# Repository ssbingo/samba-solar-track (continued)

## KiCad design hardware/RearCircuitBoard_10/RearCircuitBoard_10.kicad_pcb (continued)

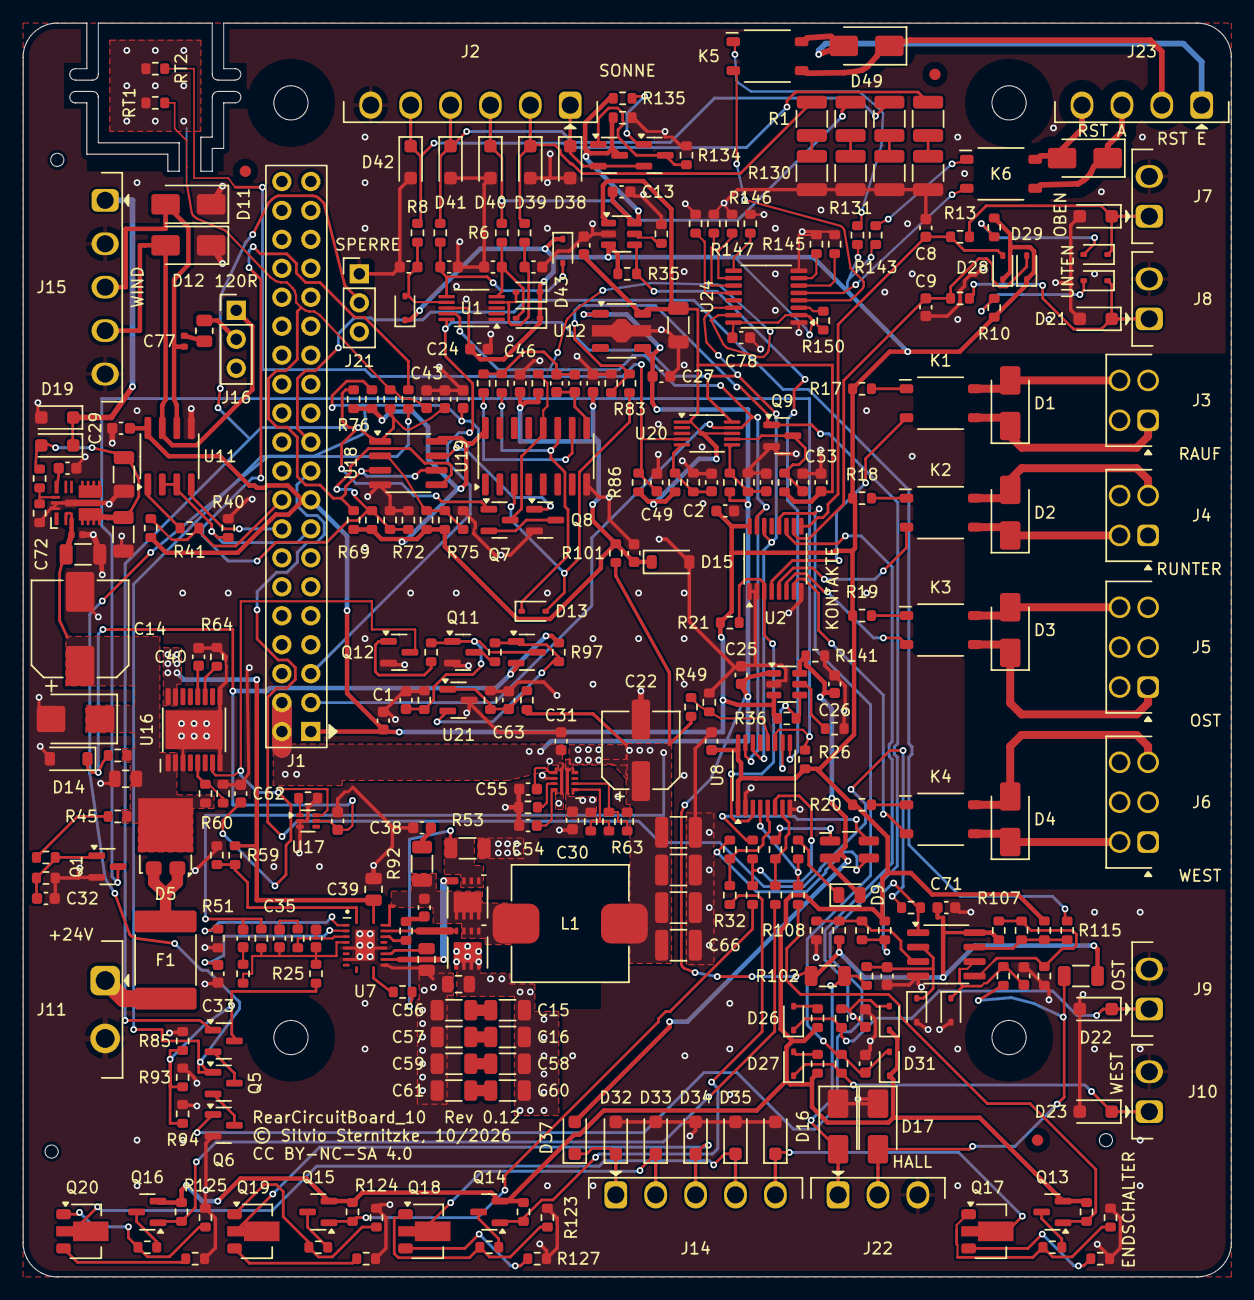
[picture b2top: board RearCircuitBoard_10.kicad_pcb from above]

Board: 4 copper layers, 106.0 x 110.0 mm, 345 parts (1 on the bottom side), 188 nets.

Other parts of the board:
FID1, FID2, FID3: Passermarke_1mm
TH1, TH2, TH3: Werkzeugloch_1.152mm

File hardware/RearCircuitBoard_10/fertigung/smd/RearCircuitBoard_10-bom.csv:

Comment,Designator,Footprint,JLCPCB Part #
10u,"C1,C13,C26,C27",C_0603_1608Metric,C19702
100n,"C2,C3,C12,C18,C24,C25,C29,C30,C32,C42,C43,C44,C45,C46,C48,C49,C50,C51,C52,C53,C71,C78",C_0603_1608Metric,C14663
4n7,"C4,C5,C6,C7,C8,C9,C10,C11",C_0603_1608Metric,C53987
100u 63V,C14,CP_Elec_8x10,C487384
2u2 100V,"C15,C16,C56,C57,C58,C59,C60,C61,C72",C_1206_3216Metric,C16195971
100n 100V,"C17,C39,C41",C_0805_2012Metric,C3011698
47u 10V,"C20,C21,C65,C66",C_1210_3225Metric,C7198516
220u 16V,C22,CP_Elec_6.3x7.7,C709481
22u 25V,"C28,C75,C76",C_1206_3216Metric,C12891
10u,C31,C_0603_1608Metric,C2959727
47n,"C33,C40",C_0603_1608Metric,C1622
2u2 25V,C34,C_0805_2012Metric,C19110
22n,C35,C_0603_1608Metric,C21122
22p,C36,C_0603_1608Metric,C1653
1n,"C37,C63,C69,C70",C_0603_1608Metric,C1588
220n,"C47,C67",C_0603_1608Metric,C21120
10n,"C54,C62,C64",C_0603_1608Metric,C57112
2n2,C55,C_0603_1608Metric,C1604
1u,"C68,C74",C_0603_1608Metric,C15849
100n 100V,C73,C_0402_ohne_Druck,C3869216
10n 100V,C77,C_0402_ohne_Druck,C527014
SMAJ33CA,"D1,D2,D3,D4,D11,D12,D16,D17,D49,D50",D_SMA,C115251
SS10P6,D5,TO-277A,C2927414
SMBJ30A,D6,D_SMB,C113998
gruen (BEREIT),D9,LED_0805_2012Metric,C2297
RGB (FAIL),D10,LED_RGB_PLCC4_S4-3528RGBTA,C2827321
1N4148WS,"D13,D24,D25,D26,D27,D28,D29,D30,D31,D43,D44,D45,D46",D_SOD-323,C2128
BZT52C5V1,D14,D_SOD-123,C173407
BZT52C5V6,D15,D_SOD-123,C19077402
MBR1H100SF,"D18,D37",D_SOD-123F,C235757
SMF30A,"D19,D20,D21,D22,D23,D32,D33,D34,D35,D36,D38,D39,D40,D41,D42",D_SOD-123F,C364281
BZT52C12S,"D47,D48",D_SOD-323,C19077447
BSMD2920-200-60V,F1,Fuse_2920_7451Metric,C49233174
AQY212GS,"K1,K2,K3,K4,K5,K6",SOP-4_4.4x4.3mm_P2.54mm_Panasonic,C415471
10u,L1,L_Wuerth_WE-LHMI_1040,C1519857
MMBT3904,"Q1,Q11,Q12",SOT-23,C20526
CSD18543Q3A,"Q2,Q3",TI_DNH0008A_CSD18543Q3A,C840100
2N7002,"Q4,Q5,Q6,Q7,Q8,Q9",SOT-23,C8545
SS8550,"Q10,Q13,Q14,Q15,Q16,Q22",SOT-23,C8542
BCX56,"Q17,Q18,Q19,Q20",SOT-89-3,C24280
SSM3J351R,Q21,SOT-23,C150147
100,"R1,R2,R3,R4,R130,R131,R132,R133",R_1210_3225Metric,C620661
22k,"R5,R6,R7,R8,R13,R14,R15,R16,R100,R136",R_0603_1608Metric,C31850
2k2,"R9,R10,R11,R12,R27,R29,R137,R138,R139,R140",R_0603_1608Metric,C4190
270,"R17,R18,R19,R20,R142,R143",R_0603_1608Metric,C22966
10k,"R21,R31,R32,R33,R34,R35,R36,R40,R42,R48,R66,R83,R99,R104,R105,R108,R109,R112,R113,R144,R145,R146,R147,R148,R149,R150",R_0603_1608Metric,C25804
200k,"R22,R26",R_0603_1608Metric,C25811
"79k6 0,1%",R24,R_0603_1608Metric,C861560
"15k 0,1%",R25,R_0603_1608Metric,C326733
1k,"R28,R30,R41,R55",R_0603_1608Metric,C21190
120,R39,R_0805_2012Metric,C17437
680,"R43,R52",R_0603_1608Metric,C23228
100k,"R45,R46,R50,R76,R77,R82,R87,R88,R89,R90,R91,R116,R118,R119,R120,R121,R134",R_0603_1608Metric,C25803
12k,"R47,R106,R107",R_0603_1608Metric,C22790
47k,"R49,R73,R74,R98,R110,R111",R_0603_1608Metric,C25819
33k,"R51,R68,R86,R95",R_0603_1608Metric,C4216
10m,R53,R_1206_3216Metric,C2076185
9k1,"R54,R117",R_0603_1608Metric,C23260
0,R58,R_0603_1608Metric,C21189
150k,R59,R_0603_1608Metric,C22807
15k,"R60,R85,R93,R94",R_0603_1608Metric,C22809
"324k 0,1%",R61,R_0603_1608Metric,C3999394
"64k9 0,1%",R62,R_0603_1608Metric,C861510
"100k 0,1%",R63,R_0603_1608Metric,C122538
6k8,"R64,R97",R_0603_1608Metric,C23212
300k,R65,R_0603_1608Metric,C23024
332k,R67,R_0603_1608Metric,C23139
56k,R69,R_0603_1608Metric,C23206
20k,R70,R_0603_1608Metric,C4184
13k,"R71,R72",R_0603_1608Metric,C22797
3k,R75,R_0603_1608Metric,C4211
2M,"R78,R79",R_0603_1608Metric,C22976
470k,"R80,R135",R_0603_1608Metric,C23178
1M,"R81,R84",R_0603_1608Metric,C22935
8k2,R96,R_0603_1608Metric,C25981
100,"R101,R114,R115",R_0603_1608Metric,C22775
4k7,"R102,R103",R_1206_3216Metric,C17936
1k5,"R122,R123,R124,R125",R_0603_1608Metric,C22843
75,"R126,R127,R128,R129",R_0603_1608Metric,C4275
4k7,R141,R_0603_1608Metric,C23162
NCU18XH103F60RB,"RT1,RT2",R_0603_1608Metric,C440252
ADS1115IDGS,"U1,U20",VSSOP-10_3x3mm_P0.5mm,C37593
PCA9538PW,"U2,U8,U24",TSSOP-16_4.4x5mm_P0.65mm,C201530
TPS2553DBV,"U5,U9",SOT-23-6,C55266
LM5146QRGYTQ1,U7,TI_RGY0020B_VQFN-20_Vias,C2876733
THVD2410DR,U11,SOIC-8_3.9x4.9mm_P1.27mm,C1849398
AP7361C-33Y5-13,U12,SOT-89-5,C460397
TPS259470ARPWR,U15,TI_RPW0010A_VQFN-HR-10,C3662799
TPS26600PWPR,U16,TI_PWP0016A_HTSSOP-16_Vias,C544399
TMP390A2DRLR,U17,SOT-563,C5219772
LM2903BIDR,"U18,U22",SOIC-8_3.9x4.9mm_P1.27mm,C2869804
74HC4060D,U19,SOIC-16_3.9x9.9mm_P1.27mm,C5649
TLV431BIDBZR,U21,SOT-23,C398375
TPSM365R6RDNR,U23,TI_RDN0011A_QFN-FCMOD-11,C20346008
